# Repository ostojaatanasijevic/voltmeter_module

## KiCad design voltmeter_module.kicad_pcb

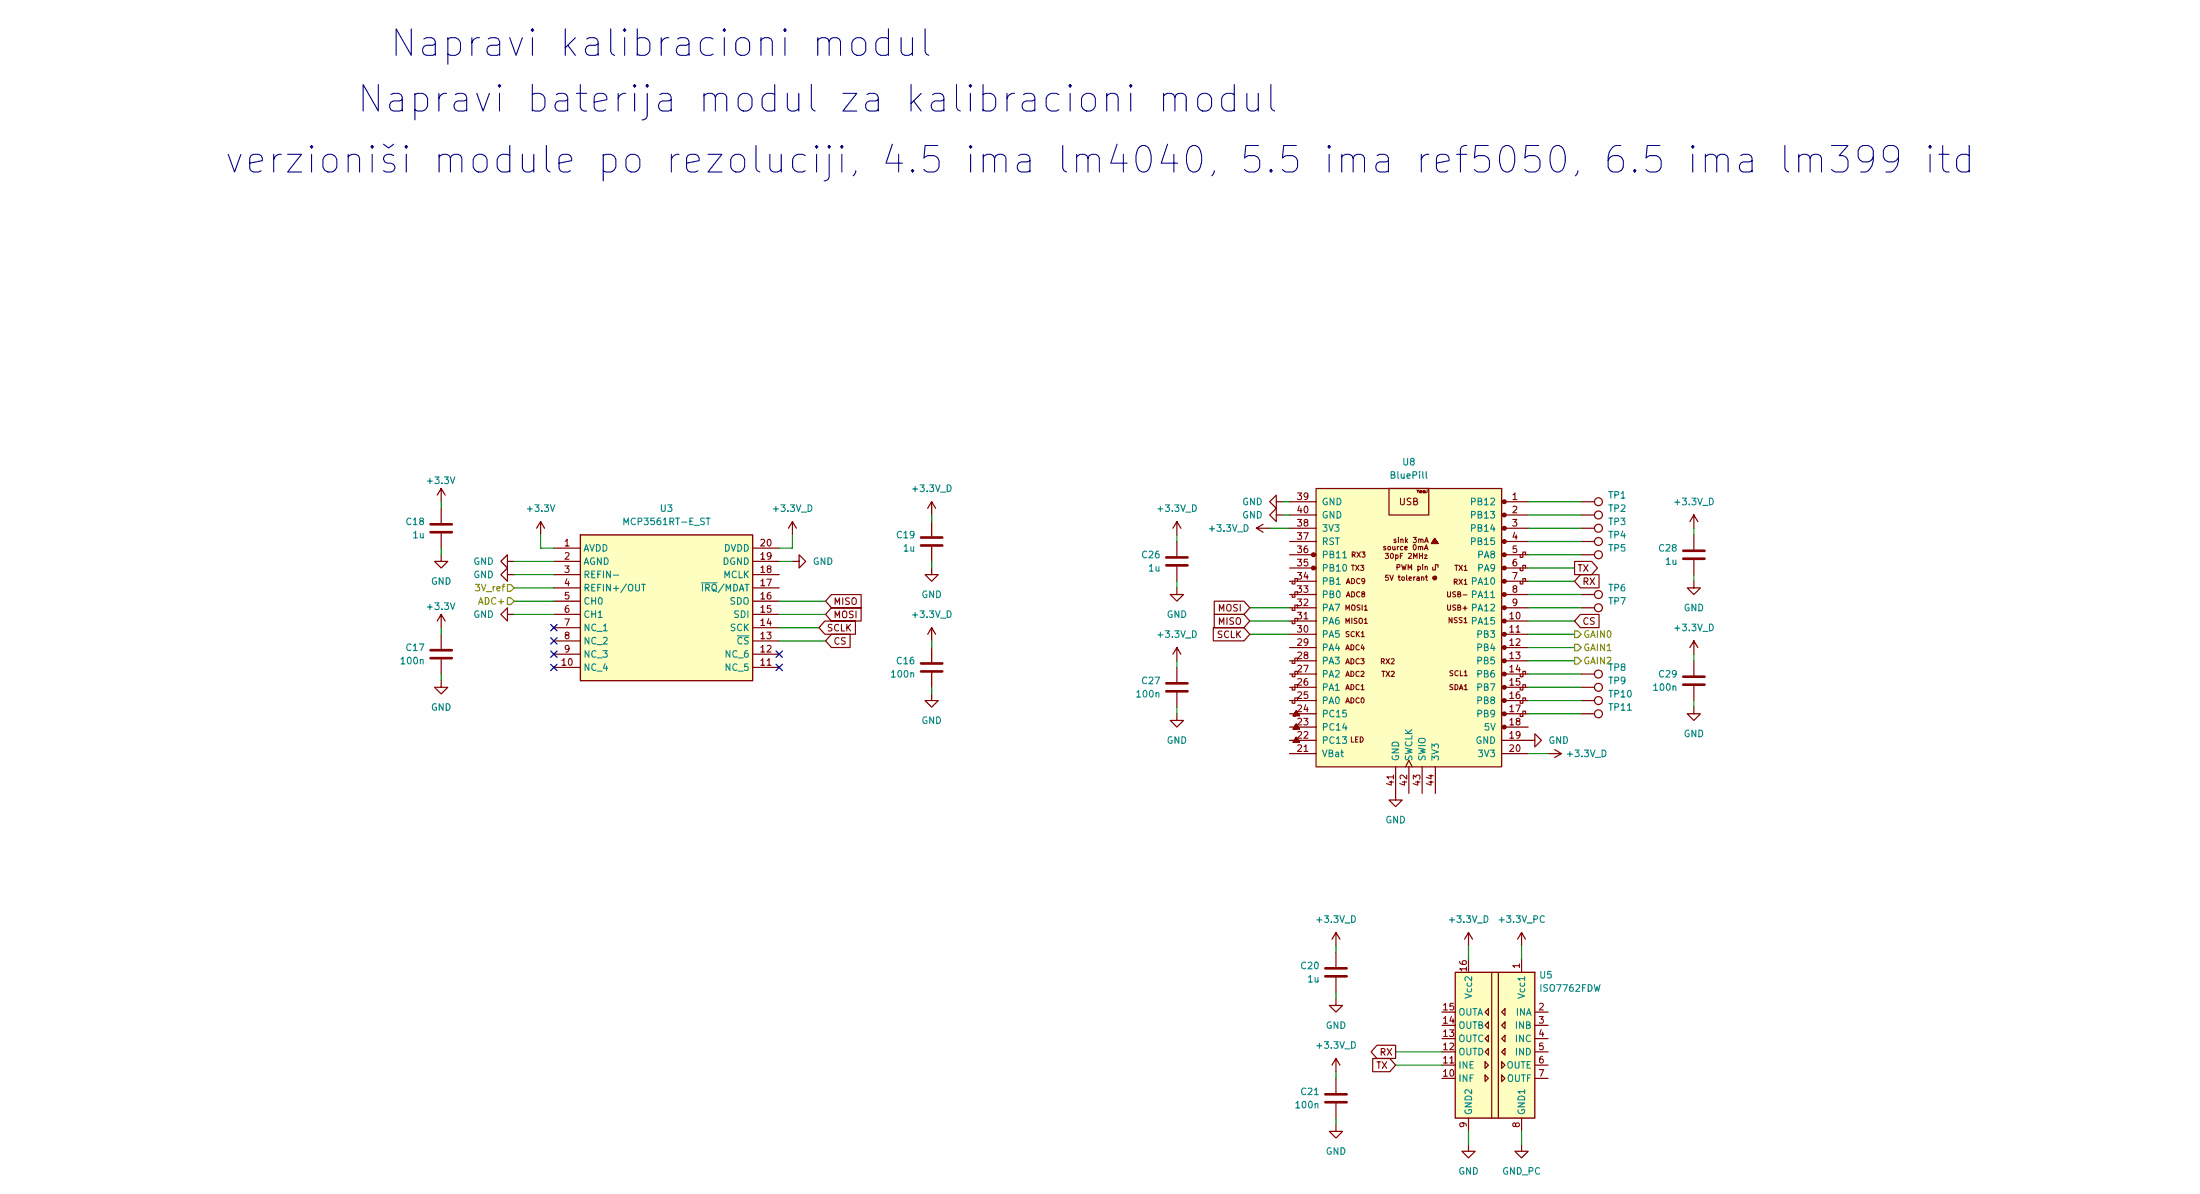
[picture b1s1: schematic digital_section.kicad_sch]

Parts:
C16, C17, C21, C27, C29: 100n; C_0603_1608Metric_Pad1.08x0.95mm_HandSolder
C18, C19, C20, C26, C28: 1u; C_0603_1608Metric_Pad1.08x0.95mm_HandSolder
TP1, TP2, TP3, TP4, TP5, TP6, TP7, TP8, TP9, TP10, TP11: TestPoint; TestPoint_Pad_D3.0mm
U3: MCP3561RT-E_ST; TSSOP-20_4.4x6.5mm_P0.65mm; Mouser Part Number 579-MCP3561RT-E/ST
U5: ISO7762FDW; SOIC-16W_7.5x10.3mm_P1.27mm
U8: BluePill

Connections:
+3.3V: C17.2, C18.2, U3.1 (AVDD); also elsewhere on the board
+3.3V_D: C16.2, C19.2, C20.2, C21.2, C26.2, C27.2, C28.2, C29.2, U3.20 (DVDD), U5.16 (Vcc2), U8.20 (3V3), U8.38 (3V3); also elsewhere on the board
+3.3V_PC: U5.1 (Vcc1); also elsewhere on the board
/Digital section/3V_ref: U3.4 (REFIN+/OUT); also elsewhere on the board
/Digital section/ADC+: U3.5 (CH0); also elsewhere on the board
CS: U3.13 (~CS), U8.10 (PA15)
GND_PC: U5.8 (GND1); also elsewhere on the board
INPUT-: C16.1, C17.1, C18.1, C19.1, C20.1, C21.1, C26.1, C27.1, C28.1, C29.1, U3.2 (AGND), U3.3 (REFIN-), U3.6 (CH1), U3.19 (DGND), U5.9 (GND2), U8.19 (GND), U8.39 (GND), U8.40 (GND), U8.41 (GND); also elsewhere on the board
MISO: U3.16 (SDO), U8.31 (PA6)
MOSI: U3.15 (SDI), U8.32 (PA7)
unnamed: TP5.1, U8.5 (PA8)
unnamed: TP6.1, U8.8 (PA11)
unnamed: TP7.1, U8.9 (PA12)
unnamed: TP8.1, U8.14 (PB6)
unnamed: TP9.1, U8.15 (PB7)
unnamed: TP10.1, U8.16 (PB8)
unnamed: TP11.1, U8.17 (PB9)
unnamed: TP1.1, U8.1 (PB12)
unnamed: TP2.1, U8.2 (PB13)
unnamed: TP3.1, U8.3 (PB14)
unnamed: TP4.1, U8.4 (PB15)
RX: U5.12 (OUTD), U8.7 (PA10)
SCLK: U3.14 (SCK), U8.30 (PA5)
TX: U5.11 (INE), U8.6 (PA9)

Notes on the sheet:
verzioniši module po rezoluciji, 4.5 ima lm4040, 5.5 ima ref5050, 6.5 ima lm399 itd
Napravi kalibracioni modul
Napravi baterija modul za kalibracioni modul

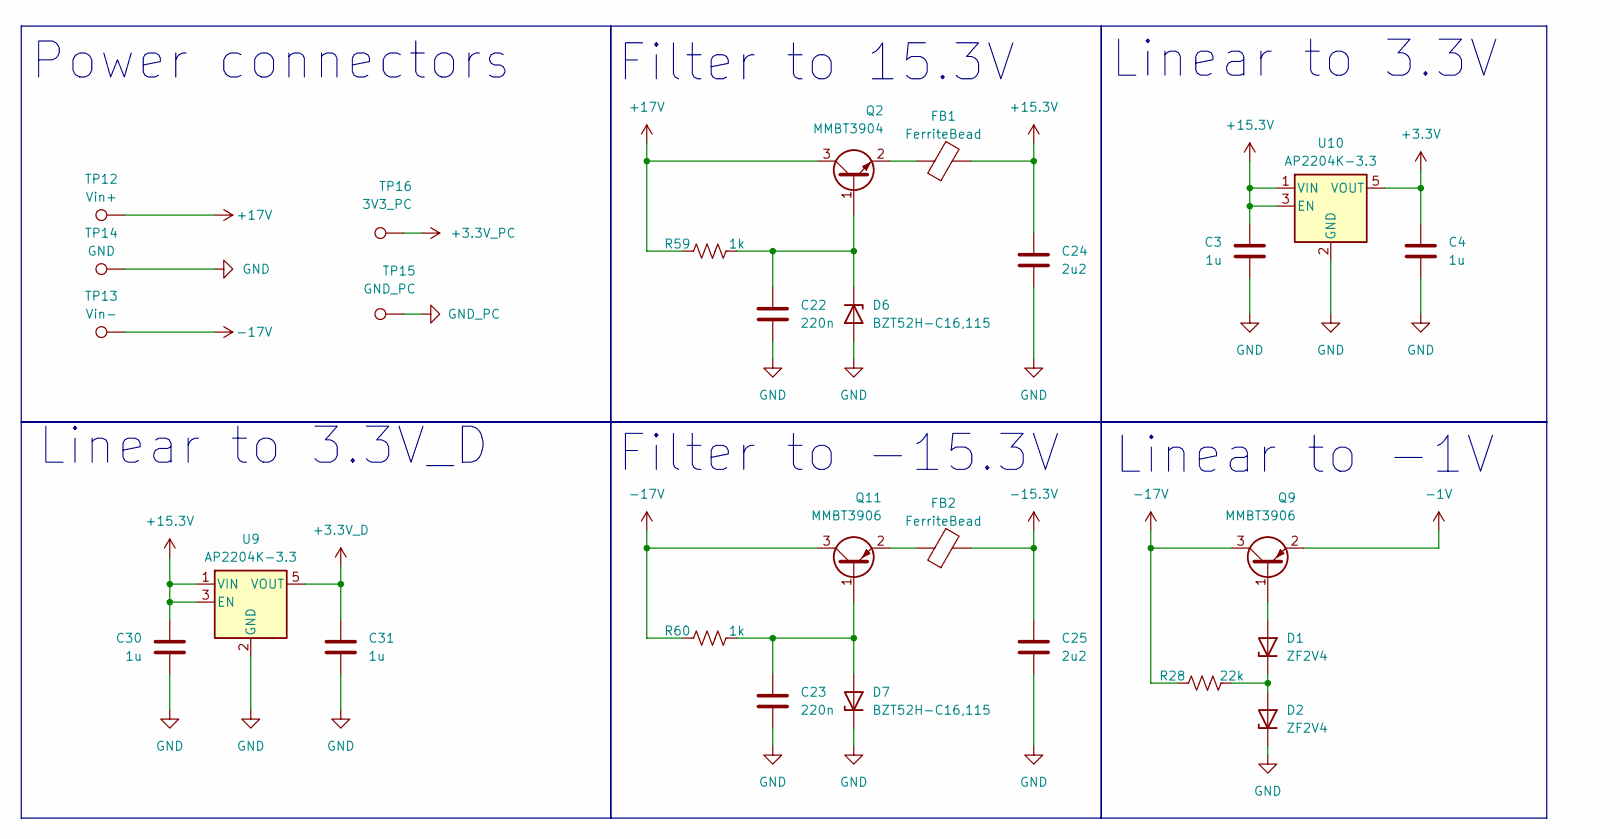
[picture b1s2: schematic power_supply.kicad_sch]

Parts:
C3, C4, C30, C31: 1u; R_0603_1608Metric_Pad0.98x0.95mm_HandSolder
C22, C23: 220n; R_0603_1608Metric_Pad0.98x0.95mm_HandSolder
C24, C25: 2u2; R_1206_3216Metric_Pad1.30x1.75mm_HandSolder
D1, D2: ZF2V4; D_DO-35_SOD27_P7.62mm_Horizontal
D6, D7: BZT52H-C16,115; D_SOD-123F
FB1, FB2: FerriteBead
Q2: MMBT3904; SOT-23
Q9, Q11: MMBT3906; SOT-23
R28: 22k; R_0603_1608Metric_Pad0.98x0.95mm_HandSolder
R59, R60: 1k; R_0603_1608Metric_Pad0.98x0.95mm_HandSolder
TP12: Vin+; TestPoint_THTPad_D4.0mm_Drill2.0mm
TP13: Vin-; TestPoint_THTPad_D4.0mm_Drill2.0mm
TP14: GND; TestPoint_THTPad_D4.0mm_Drill2.0mm
TP15: GND_PC; TestPoint_THTPad_D4.0mm_Drill2.0mm
TP16: 3V3_PC; TestPoint_THTPad_D4.0mm_Drill2.0mm
U9, U10: AP2204K-3.3; SOT-23-5

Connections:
+3.3V: C4.1, U10.5 (VOUT); also elsewhere on the board
+3.3V_D: C31.1, U9.5 (VOUT); also elsewhere on the board
+3.3V_PC: TP16.1; also elsewhere on the board
+15.3V: C3.1, C24.2, C30.1, FB1.2, U9.1 (VIN), U9.3 (EN), U10.1 (VIN), U10.3 (EN); also elsewhere on the board
+17V: Q2.3 (C), R59.2, TP12.1
-1V: Q9.2 (E); also elsewhere on the board
-15.3V: C25.2, FB2.2; also elsewhere on the board
-17V: Q9.3 (C), Q11.3 (C), R28.2, R60.2, TP13.1
GND_PC: TP15.1; also elsewhere on the board
INPUT-: C3.2, C4.2, C22.2, C23.2, C24.1, C25.1, C30.2, C31.2, D2.1 (K), D6.2 (A), D7.1 (K), TP14.1, U9.2 (GND), U10.2 (GND); also elsewhere on the board
unnamed: D1.2 (A), Q9.1 (B)
unnamed: D1.1 (K), D2.2 (A), R28.1
unnamed: C22.1, D6.1 (K), Q2.1 (B), R59.1
unnamed: C23.1, D7.2 (A), Q11.1 (B), R60.1
unnamed: FB1.1, Q2.2 (E)
unnamed: FB2.1, Q11.2 (E)

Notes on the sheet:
Linear to 3.3V_D
Filter to 15.3V
Linear to -1V
Power connectors
Linear to 3.3V
Filter to -15.3V

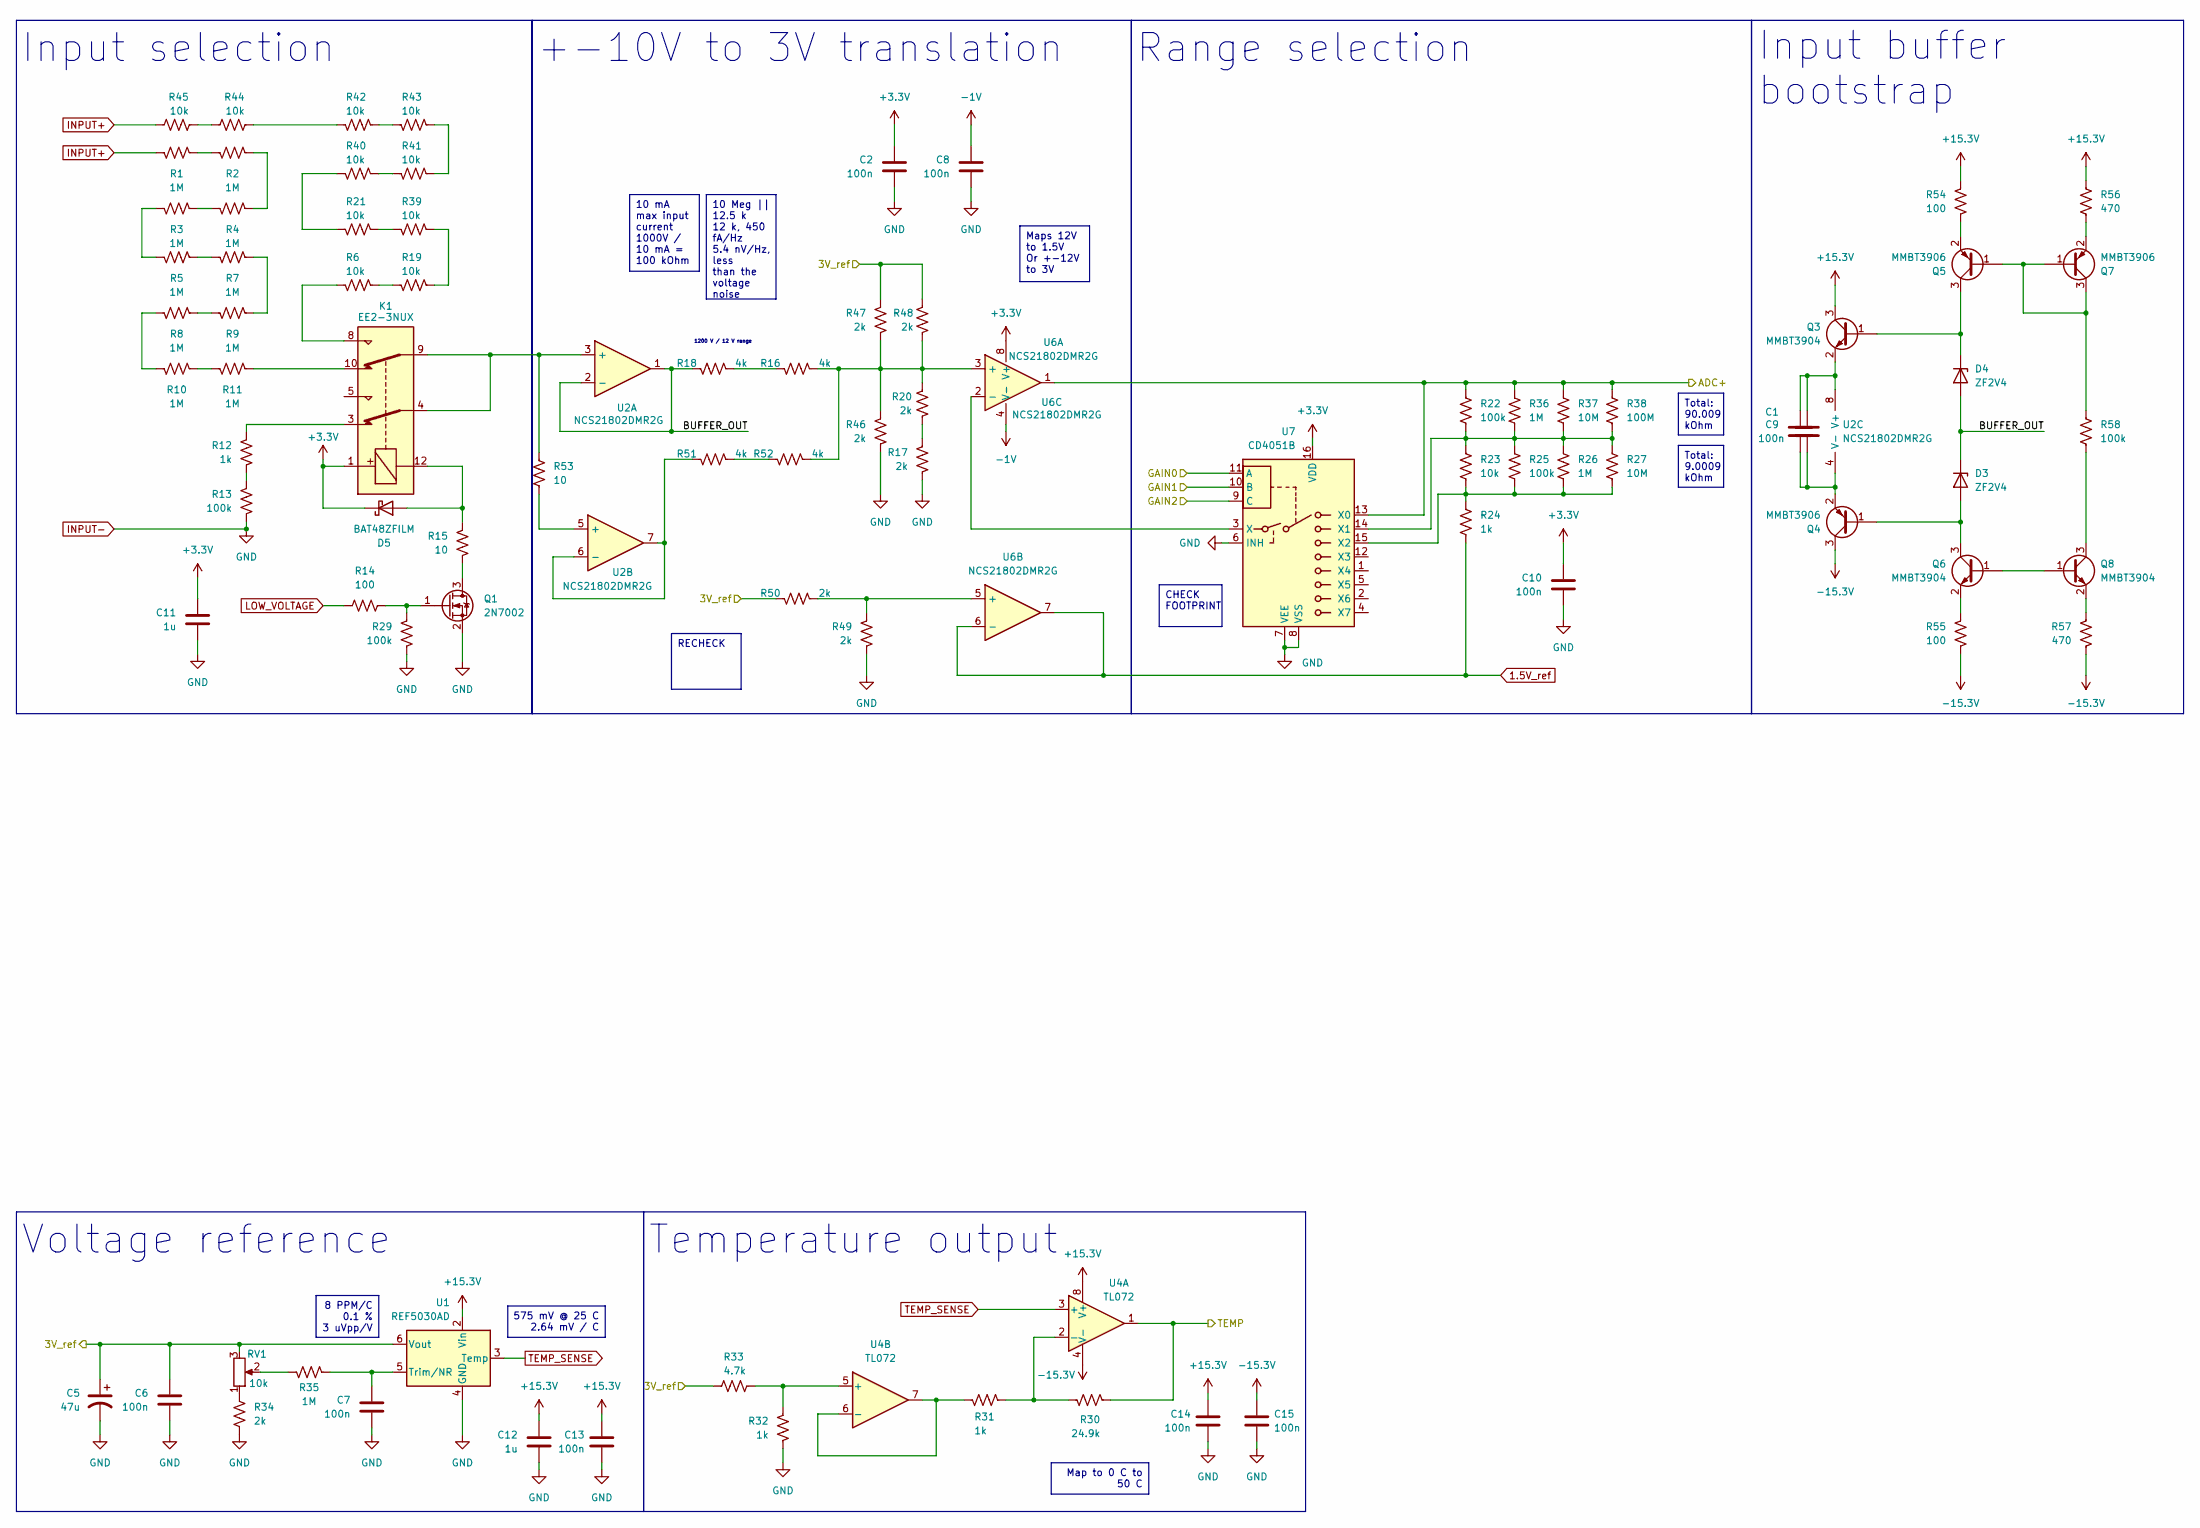
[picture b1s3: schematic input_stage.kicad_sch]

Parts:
C1, C2, C6, C7, C8, C9, C10, C13, C14, C15: 100n; C_0603_1608Metric_Pad1.08x0.95mm_HandSolder
C5: 47u; CP_Radial_D5.0mm_P2.00mm
C11, C12: 1u; C_0603_1608Metric_Pad1.08x0.95mm_HandSolder
D3, D4: ZF2V4; D_DO-35_SOD27_P7.62mm_Horizontal
D5: BAT48ZFILM; D_SOD-123
K1: EE2-3NUX; Relay_DPDT_Kemet_EE2_NUX_NKX
Q1: 2N7002; SOT-23
Q3, Q6, Q8: MMBT3904; SOT-23
Q4, Q5, Q7: MMBT3906; SOT-23
R1, R2, R3, R4, R5, R7, R8, R9, R10, R11: 1M; R_1206_3216Metric_Pad1.30x1.75mm_HandSolder
R6, R19, R21, R23, R39, R40, R41, R42, R43, R44, R45: 10k; R_0603_1608Metric_Pad0.98x0.95mm_HandSolder
R12, R24, R31, R32: 1k; R_0603_1608Metric_Pad0.98x0.95mm_HandSolder
R13, R22, R25, R29, R58: 100k; R_0603_1608Metric_Pad0.98x0.95mm_HandSolder
R14, R54, R55: 100; R_0603_1608Metric_Pad0.98x0.95mm_HandSolder
R15, R53: 10; R_0603_1608Metric_Pad0.98x0.95mm_HandSolder
R16, R18, R51, R52: 4k; R_0603_1608Metric_Pad0.98x0.95mm_HandSolder
R17, R20, R34, R46, R47, R48, R49, R50: 2k; R_0603_1608Metric_Pad0.98x0.95mm_HandSolder
R26, R35, R36: 1M; R_0603_1608Metric_Pad0.98x0.95mm_HandSolder
R27, R37: 10M; R_0603_1608Metric_Pad0.98x0.95mm_HandSolder
R30: 24.9k; R_0603_1608Metric_Pad0.98x0.95mm_HandSolder
R33: 4.7k; R_0603_1608Metric_Pad0.98x0.95mm_HandSolder
R38: 100M; R_0603_1608Metric_Pad0.98x0.95mm_HandSolder
R56, R57: 470; R_0603_1608Metric_Pad0.98x0.95mm_HandSolder
RV1: 10k; Potentiometer_Bourns_3296W_Vertical
U1: REF5030AD; SOIC-8_3.9x4.9mm_P1.27mm
U2, U6: NCS21802DMR2G; OnSemi_Micro8
U4: TL072; SOIC-8_3.9x4.9mm_P1.27mm
U7: CD4051B; SOIC-16_3.9x9.9mm_P1.27mm

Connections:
1.5V_ref: R24.1, U6.6 (-), U6.7
+3.3V: C2.2, C10.2, C11.2, D5.1 (K), K1.1, U6.8 (V+), U7.16 (VDD); also elsewhere on the board
+15.3V: C12.2, C13.2, C14.2, Q3.3 (C), R54.2, R56.2, U1.2 (Vin), U4.8 (V+); also elsewhere on the board
-1V: C8.2, U6.4 (V-); also elsewhere on the board
-15.3V: C15.2, Q4.3 (C), R55.1, R57.1, U4.4 (V-); also elsewhere on the board
/Digital section/3V_ref: R22.2, R36.2, R37.2, R38.2, U6.1, U7.13 (X0); also elsewhere on the board
/Digital section/ADC+: C5.1, C6.2, R33.1, R47.2, R48.2, R50.2, RV1.3, U1.6 (Vout); also elsewhere on the board
/Digital section/GAIN0: U7.11 (A)
/Digital section/GAIN1: U7.10 (B)
/Digital section/GAIN2: U7.9 (C)
/Input stage/BUFFER_OUT: D3.1 (K), D4.2 (A), R18.2, U2.1, U2.2 (-)
/Input stage/TEMP: R30.1, U4.1
INPUT+: R1.1, R45.2
INPUT-: C2.1, C5.2, C6.1, C7.1, C8.1, C10.1, C11.1, C12.1, C13.1, C14.1, C15.1, Q1.2 (S), R13.1, R17.1, R29.1, R32.1, R34.1, R46.1, R49.1, U1.4 (GND), U7.6 (INH), U7.7 (VEE), U7.8 (VSS); also elsewhere on the board
LOW_VOLTAGE: R14.2
unnamed: D3.2 (A), Q4.1 (B), Q6.3 (C)
unnamed: D4.1 (K), Q3.1 (B), Q5.3 (C)
unnamed: D5.2 (A), K1.12, R15.2
unnamed: K1.3, R12.2
unnamed: K1.8, R6.1
unnamed: K1.10, R11.2
unnamed: Q1.3 (D), R15.1
unnamed: Q1.1 (G), R14.1, R29.2
unnamed: C1.2, C9.2, Q3.2 (E), U2.8 (V+)
unnamed: C1.1, C9.1, Q4.2 (E), U2.4 (V-)
unnamed: Q5.1 (B), Q7.1 (B), Q7.3 (C), R58.2
unnamed: Q5.2 (E), R54.1
unnamed: Q6.1 (B), Q8.1 (B)
unnamed: Q6.2 (E), R55.2
unnamed: Q7.2 (E), R56.1
unnamed: Q8.3 (C), R58.1
unnamed: Q8.2 (E), R57.2
unnamed: R1.2, R2.1
unnamed: R2.2, R4.2
unnamed: R3.1, R5.1
unnamed: R3.2, R4.1
unnamed: R5.2, R7.1
unnamed: R7.2, R9.2
unnamed: R8.2, R9.1
unnamed: R8.1, R10.1
unnamed: R10.2, R11.1
unnamed: R12.1, R13.2
unnamed: R16.2, R18.1
unnamed: R17.2, R20.1
unnamed: R6.2, R19.1
unnamed: R19.2, R39.2
unnamed: R21.1, R40.1
unnamed: R21.2, R39.1
unnamed: R34.2, RV1.1
unnamed: R35.2, RV1.2
unnamed: R40.2, R41.1
unnamed: R41.2, R43.2
unnamed: R42.1, R44.1
unnamed: R42.2, R43.1
unnamed: R44.2, R45.1
unnamed: R51.1, R52.2
unnamed: C7.2, R35.1, U1.5 (Trim/NR)
unnamed: K1.4, K1.9, R53.2, U2.3 (+)
unnamed: R53.1, U2.5 (+)
unnamed: R51.2, U2.6 (-), U2.7
unnamed: R30.2, R31.2, U4.2 (-)
unnamed: R32.2, R33.2, U4.5 (+)
unnamed: R31.1, U4.6 (-), U4.7
unnamed: R16.1, R20.2, R46.2, R47.1, R48.1, R52.1, U6.3 (+)
unnamed: U6.2 (-), U7.3 (X)
unnamed: R49.2, R50.1, U6.5 (+)
unnamed: R22.1, R23.2, R25.2, R26.2, R27.2, R36.1, R37.1, R38.1, U7.14 (X1)
unnamed: R23.1, R24.2, R25.1, R26.1, R27.1, U7.15 (X2)
TEMP_SENSE: U1.3 (Temp), U4.3 (+)

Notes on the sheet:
CHECK FOOTPRINT
8 PPM/C 0.1 % 3 uVpp/V
575 mV @ 25 C 2.64 mV / C
Maps 12V to 1.5V Or +-12V to 3V
Total: 90.009 kOhm
Map to 0 C to 50 C
RECHECK
10 Meg || 12.5 k 12 k, 450 fA/Hz 5.4 nV/Hz, less than the voltage noise
10 mA max input current 1000V / 10 mA = 100 kOhm
Total: 9.0009 kOhm
Temperature output
Input buffer bootstrap
Range selection
Input selection
+-10V to 3V translation
1200 V / 12 V range
Voltage reference

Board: 2 copper layers, 135 parts (0 on the bottom side), 74 nets, no tracks yet.

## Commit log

2024-10-29 Init.
2024-10-29 To je to otp
2024-10-29 Add millivolt input.
2024-10-30 Tex.
2024-10-30 Not much. Not much.
2024-10-30 TL072 for the win.
2024-10-31 tiny.
2024-11-03 Added temperature, ref trimming and range selection resisitors.
2024-11-09 Fixed diff amp.
2024-11-09 Recheck
2024-11-10 RM backup.
2024-11-10 Improved gain stage.
2024-11-12 sqrt2 noise
2024-11-12 fixed resistor
2024-11-13 on MCU
    on MCU
2025-01-07 fsda
2025-01-10 Bootstraped input buffer.
2025-01-19 Mora se poraditi na MCK pinu.
